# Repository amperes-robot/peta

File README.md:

ENPH 253 Project Repository

Team PETA
=========

Kevin Zhang

Anne Lim

Scott Fjordbotten

Johnson Liu

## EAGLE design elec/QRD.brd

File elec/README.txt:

Files for electrical design and simulations.

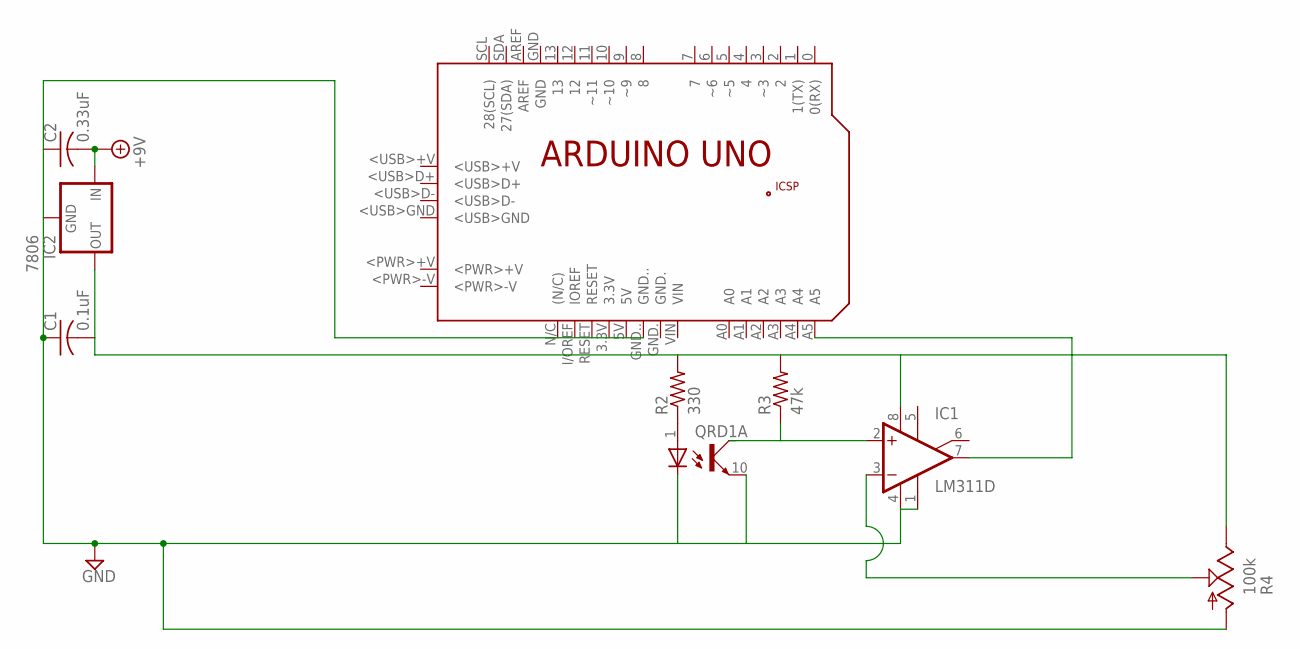
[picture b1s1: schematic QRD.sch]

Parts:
C1: 0.1uF; C025-024X044
C2: 0.33uF; C025-024X044
IC1: LM311D; SO08
IC2: 7806; 78XXL
PCB1: ARDUINO_UNO
QRD1: SFH6943; SOT223/10
R2: 330; 0204V
R3: 47k; 0204V
R4: 100k; 3223G

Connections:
+9V: C2.2, IC2.IN
GND: C1.1, C2.1, IC1.1 (GND), IC1.4 (V-), IC2.GND, PCB1.GND.., QRD1.10 (EMI), R4.1 (A)
unnamed: IC1.7 (OUT), PCB1.A5
unnamed: QRD1.1 (A), R2.1
unnamed: IC1.3 (-IN), R4.2 (S)
unnamed: IC1.2 (+IN), R3.1
unnamed: C1.2, IC1.8 (V+), IC2.OUT, R2.2, R3.2, R4.3 (E)

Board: 2 copper layers, 9 parts (2 on the bottom side), 7 nets, no tracks yet.

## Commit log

2015-05-13 added readme files
2015-05-13 init environment
2015-05-13 more framework stuff
2015-05-13 toolchain
2015-05-14 updated framework
2015-05-14 added enph253 lib (but it doesn't compile)
2015-05-14 updated makefile to work with cygwin
2015-05-14 begin work on simulator
2015-05-14 revoved libraries
2015-05-15 simulator works kind of
2015-05-15 simulator progress
2015-05-19 removed simulation fw, added testing
2015-05-27 remove test cpp file, add pid framework
2015-05-27 added stuff
2015-06-03 motor file
2015-06-03 chassis and rear wheel solidworks stuff
2015-06-03 remove temp solidworks files
2015-06-03 removed autogenerated files and updated gitignore
2015-06-04 move wheels in
2015-06-09 arm and chissis mods
2015-06-09 end of day june 8
2015-06-09 played with some geometry
2015-06-09 part mods
2015-06-10 june 09 2015
2015-06-10 isrs
2015-06-10 more interrupts and raw analog reading
2015-06-10 removed testing framework (kind of useless)
2015-06-11 a bunch of arm stuff June10th
2015-06-11 add sled
2015-06-11 make chassis assembly to clean up main assembly
2015-06-11 menu modes
2015-06-11 adc interrupt
2015-06-12 add tinah mount and pet removal tool
2015-06-12 front arm for pet 4 and random mods
2015-06-12 axles and rollers and assembly and cshape
2015-06-12 pid and menu
2015-06-12 menu finish
2015-06-12 clean up file storage and zipline zipper
2015-06-12 IR Detector and Filter
2015-06-13 update zipline assy as per jons advice
2015-06-13 added some sensors
2015-06-14 fixed bug where options didn't reflect
2015-06-14 disable copyctor for Opt
2015-06-14 Hbridge and IR Detector circuits modified version June 13
2015-06-14 Initial commit of 2 QRD circuits
2015-06-14 Updated QRD and created winch circuit
2015-06-14 Updated H bridge
2015-06-14 a whole bunch of stuff I dont remember including finishing the zipline stuff
2015-06-14 modified QRD added potentialmeter value
2015-06-15 Swtich for detecting pet pick up
2015-06-15 modified winch circuit
2015-06-16 IDEK
2015-06-16 Start of LaTex for Design Report
2015-06-16 I HAVE NO IDEA
2015-06-16 move report over and ignore auxilaries
2015-06-16 git made me do it
2015-06-16 add software modes table
2015-06-16 Elec tables
2015-06-16 finish elec tables
2015-06-16 update refference style
2015-06-16 begin appendix
2015-06-16 Circuit schematics initial commit for report and proposal
2015-06-16 add schematics appendix and references in elec section
2015-06-16 Letter of Transmissal
2015-06-16 appendix calculations
2015-06-16 nicer Letter
2015-06-16 Signed Letter
2015-06-16 adjusting tables
2015-06-16 Just a gear
2015-06-16 report add up to arm assy, mod some parts
2015-06-17 added risk table to latex
2015-06-17 add preface
2015-06-17 added pamela cuz shes marking :P
2015-06-17 Use this gear
2015-06-17 table formatting
2015-06-17 Sensor system done
2015-06-17 added task table
2015-06-17 Finish zipline section in report
2015-06-17 fuck my lyfe
2015-06-17 added algorithms for position correction
2015-06-17 better signatures
2015-06-17 All signed
2015-06-17 wrote drive and actuation section, formatting
2015-06-17 editing sensors section
2015-06-17 added torque calculations
2015-06-17 edit summary, add to tasks/milestones
2015-06-17 edits
2015-06-17 Voltage regulators added if necessary
2015-06-17 fix arm issue and update report
2015-06-17 voltage regulators added
2015-06-17 task list
2015-06-18 Add drive gears
2015-06-18 update report with gears
2015-06-18 fix formmating
2015-06-18 add IR circuit calculations
2015-06-18 some edits
2015-06-18 changed state diagram
2015-06-18 add zipline sensor to report
2015-06-18 Add name to report
2015-06-18 final report
2015-06-18 fixed compilation problems
2015-06-19 revamped digital io
2015-06-19 fixed io and start course
2015-06-19 add dxf files, uprev gears, add rivit holes
2015-06-19 New roller drawn, no radius of curvature at all
2015-06-19 added restore option
2015-06-19 fixed opt-restore
2015-06-19 turn off adc free running
2015-06-19 update parts add renderings
2015-06-20 continuous adc polling
2015-06-20 switch to delay_ms
2015-06-20 analog input optimizations
2015-06-20 added args to mode begin
2015-06-23 refactoring and stuff
2015-06-23 fixed analog reads
2015-06-24 added timer3 compa vect
2015-06-24 work on course logic
2015-06-24 fixed missing increment
2015-06-24 add beacon homing
2015-06-24 edits and DFXs
2015-06-25 modified gear for new wheel
2015-06-25 stuff
2015-06-26 sinetales
2015-06-27 new drive system and other shit
2015-06-29 compiles
2015-06-29 moved strings to flash
2015-06-30 update drive system
2015-07-01 more work on new drive system and progress on arm design
2015-07-02 new pid and view menu
2015-07-02 fix pid direction of recovery
2015-07-02 added mode returns
2015-07-02 fixed pid once and for all
2015-07-06 clean DXF folder
2015-07-07 arm motor encoder
2015-07-07 dxf for frontarm
2015-07-07 frontarm
2015-07-07 filleted the holes
2015-07-08 front arm L bracket
2015-07-08 mech updates
2015-07-09 zipline arm guide dxf
2015-07-09 better state machine
2015-07-10 fuck
2015-07-11 design refinenents on zipline arm
2015-07-13 arm lifting stuff
2015-07-13 add brake state
2015-07-13 parallel park mode
2015-07-14 afasfasdfasf
2015-07-14 finalize zipline
2015-07-14 fixed fsm
2015-07-14 sync follow and pid
2015-07-14 restructure with analog digital sfhoiafjdoiadjf
2015-07-15 analog 4
2015-07-15 fixed controller
2015-07-15 fix for stasis
2015-07-15 adjusting and recovery modes for pet pickup
2015-07-15 fixed not entering recovery
2015-07-15 add missing encoder update
2015-07-15 fixed sign on theta values
2015-07-15 add line detect cooldown
2015-07-16 fixed fjfsafd
2015-07-16 course calibration
2015-07-16 updated values
2015-07-16 reverse follow return
2015-07-16 new zipline delivery system
2015-07-17 fixed pet 3 not bedooj
2015-07-17 finish zipline design and DXFs
2015-07-17 update debug thing
2015-07-18 fstija
2015-07-21 code stuff
2015-07-21 fasdfjas
2015-07-21 fied adjustment values
2015-07-22 homing stuff
2015-07-22 last pet turn around and return
2015-07-22 six point run
2015-07-22 dead zone for reverse follow
2015-07-22 drive straight forward in dead zone
2015-07-22 mod to drive bracket
2015-07-22 docs
2015-07-23 parameter tweaks
2015-07-23 integrate ppark
2015-07-23 update debug mode
2015-07-23 parallel parking better
2015-07-23 better ppark
2015-07-23 new arm
2015-07-24 final pet
2015-07-24 switch from ppark to excavation
2015-07-24 move stuff to nother file
2015-07-24 fixed stuff
2015-07-24 final tweaks
2015-07-24 update shaft fitting
2015-07-28 async
2015-07-28 renamed qrd_side_left and qrd_side_right
2015-07-28 empty square functions
2015-07-28 more async stuff
2015-07-28 more stuff
2015-07-28 square stuff
2015-07-28 working squared version
2015-07-28 more conditions
2015-07-29 first pet
2015-07-29 async stff
2015-07-29 first pet properly works
2015-07-29 fixed up async
2015-07-29 arm retrieds if fails to pick up pet
2015-07-29 fixed signededness bugs
2015-07-29 tried to make stuff better and it works sometimes except for when it fails dangerously
2015-07-29 first pet navigation
2015-07-29 up to pet 3
2015-07-29 updated retrieval function
2015-07-29 dead zone for way up
2015-07-29 dead zone is encoder based
2015-07-29 beacon homing
2015-07-29 elevated pet
2015-07-29 minor changes to courseg
2015-07-30 changed parameters
2015-07-30 add excavator encoder
2015-07-30 final pet code
2015-07-30 last pet tweaks
2015-07-30 fixed overflow error
2015-07-31 updates to last pet
2015-07-31 reset mode and stuff
2015-07-31 almost got final pet
2015-07-31 working final pet code
2015-07-31 stability improvements
2015-08-01 filter for IR fioajsdfj
2015-08-01 Circuit pictures for website added
2015-08-01 sometimes works
2015-08-01 working code
2015-08-04 tentative update with better squaring
2015-08-04 updates for final tuning
2015-08-04 more tuning
2015-08-04 shortened course
2015-08-04 working sort of
2015-08-04 test 4
2015-08-05 better
2015-08-05 better squaring, kind of works
2015-08-05 arm goes down less
2015-08-05 can collect all reliably, might not return to tape
2015-08-05 can reliably return now
2015-08-05 exc comes back a little more
2015-08-05 fix short course
2015-08-05 small tweaks
2015-08-06 final state
2015-08-06 past the end
